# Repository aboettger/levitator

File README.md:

Levitator by RxBConcept on Thingiverse: https://www.thingiverse.com/thing:1966169

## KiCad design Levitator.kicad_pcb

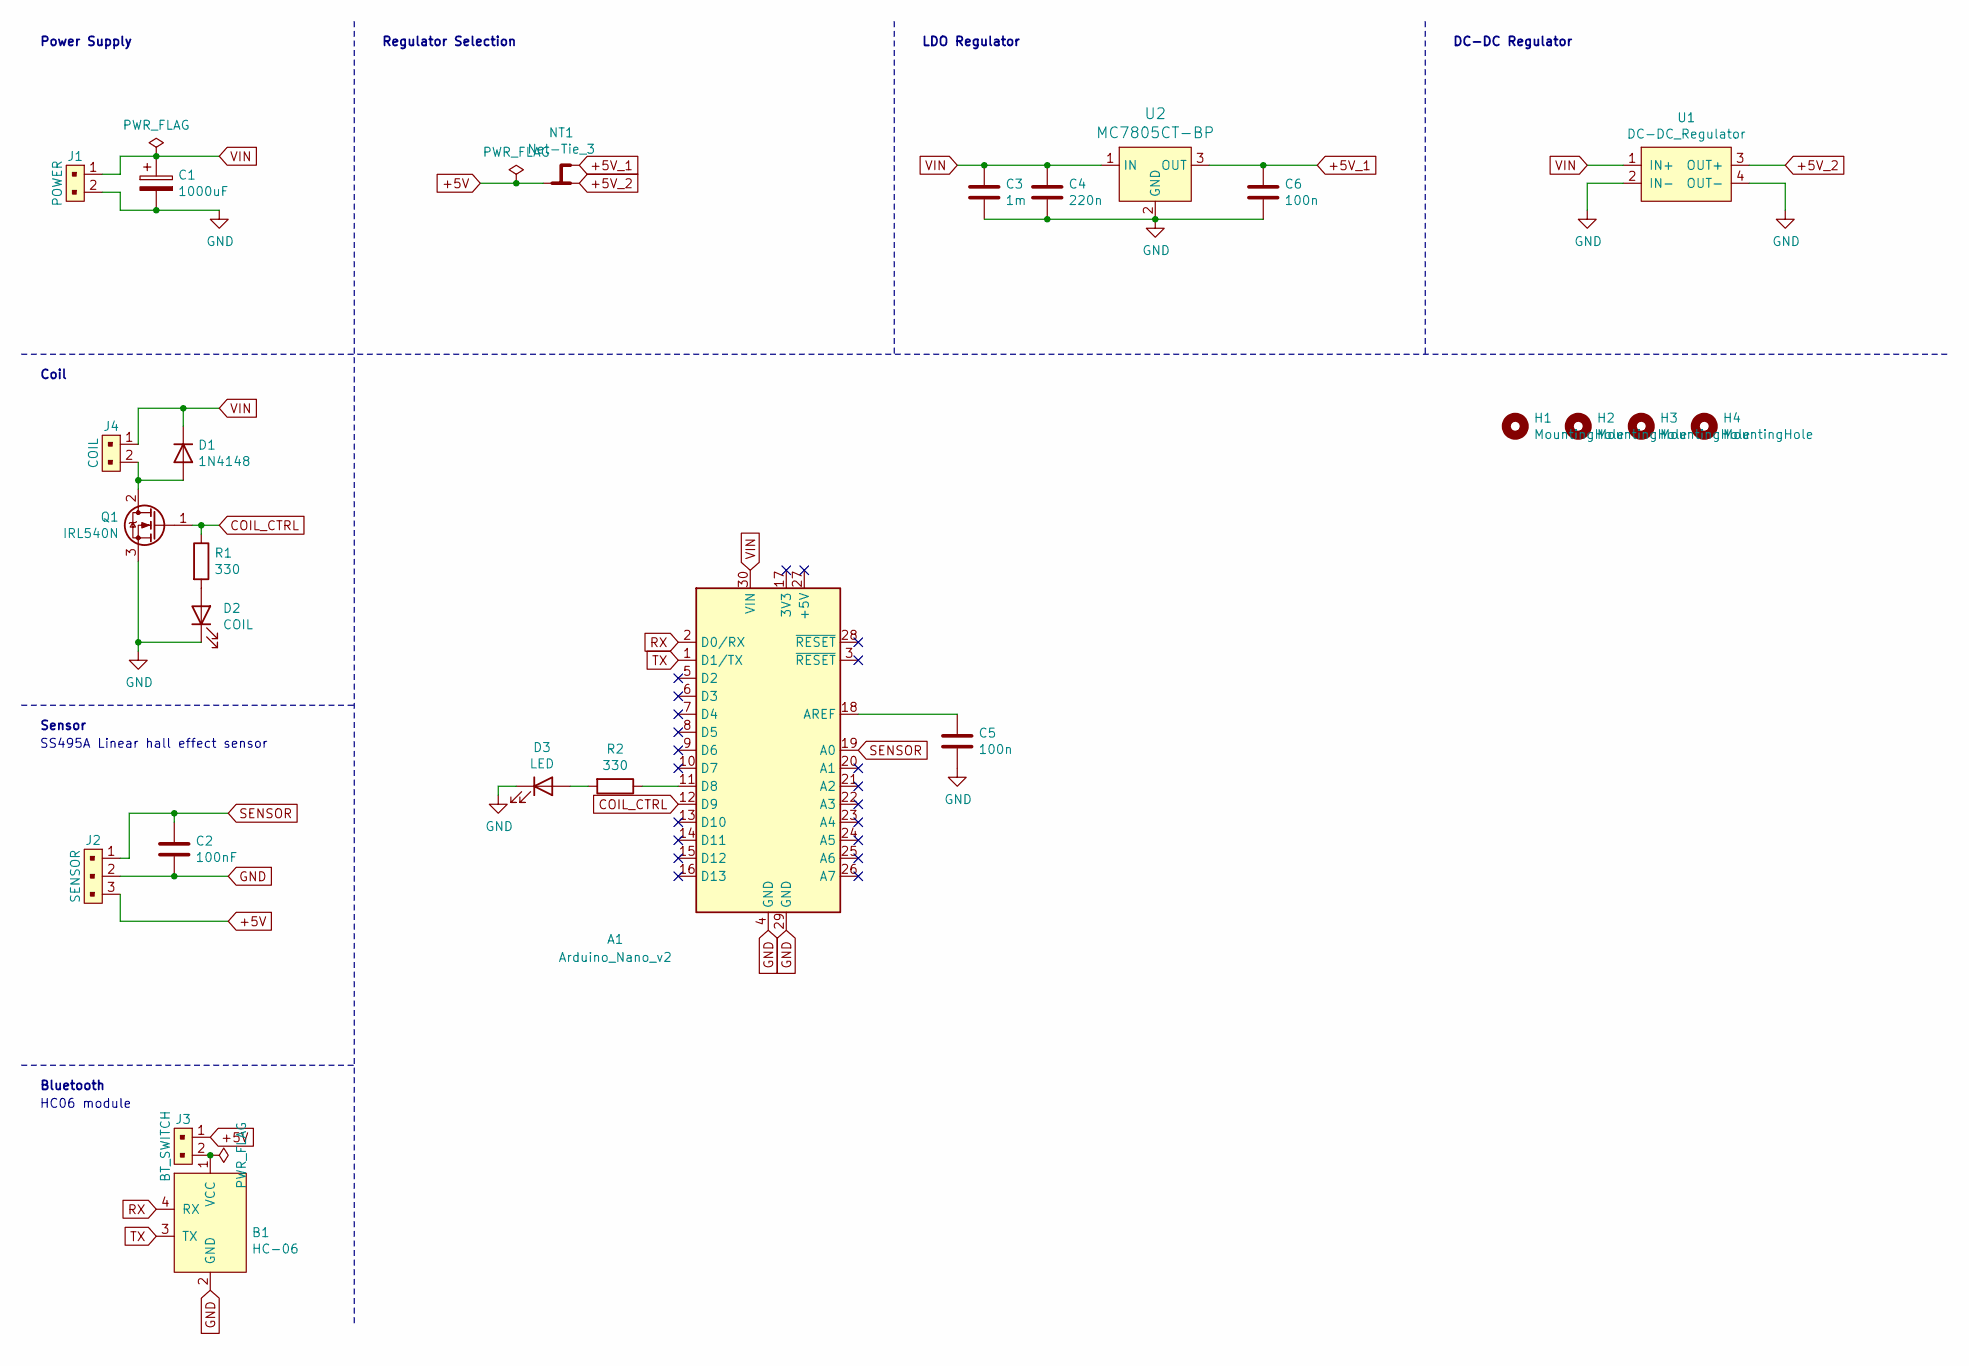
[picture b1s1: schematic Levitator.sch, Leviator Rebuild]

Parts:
A1: Arduino_Nano_v2; Arduino_Nano
B1: HC-06
C1: 1000uF; CP_Radial_D8.0mm_P3.50mm
C2: 100nF; C_Rect_L7.0mm_W2.5mm_P5.00mm
C3: 1m; C_Rect_L7.0mm_W3.5mm_P2.50mm_P5.00mm
C4: 220n; C_Rect_L7.0mm_W3.5mm_P2.50mm_P5.00mm
C5: 100n; C_Rect_L7.0mm_W2.5mm_P5.00mm
C6: 100n; C_Rect_L7.0mm_W3.5mm_P2.50mm_P5.00mm
D1: 1N4148; D_DO-35_SOD27_P7.62mm_Horizontal
D2: COIL; LED_D3.0mm
D3: LED; LED_D3.0mm
H1, H2, H3, H4: MountingHole; MountingHole_3.2mm_M3
J1: POWER; JST_EH_B2B-EH-A_1x02_P2.50mm_Vertical; MPN 22-23-2021; Digi-Key_PN WM4200-ND
J2: SENSOR; JST_EH_B3B-EH-A_1x03_P2.50mm_Vertical
J3: BT_SWITCH; JST_EH_B2B-EH-A_1x02_P2.50mm_Vertical; MPN 22-23-2021; Digi-Key_PN WM4200-ND
J4: COIL; JST_EH_B2B-EH-A_1x02_P2.50mm_Vertical; MPN 22-23-2021; Digi-Key_PN WM4200-ND
NT1: Net-Tie_3; NetTie-3_THT_Pad1.0mm
Q1: IRL540N; TO-220-3_Horizontal_TabDown
R1, R2: 330; R_Axial_DIN0204_L3.6mm_D1.6mm_P7.62mm_Horizontal
U1: DC-DC_Regulator; Board_45x20
U2: MC7805CT-BP; TO-220-3_Horizontal_TabDown; MPN MC7805CT-BP; Digi-Key_PN MC7805CT-BPMS-ND

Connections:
+5V: J2.3, J3.1, NT1.2
+5V_1: C6.1, NT1.3, U2.3 (OUT)
+5V_2: NT1.1, U1.3 (OUT+)
COIL_CTRL: A1.12 (D9), Q1.1 (G), R1.1
GND: A1.4 (GND), A1.29 (GND), B1.2 (GND), C1.2, C2.2, C3.2, C4.2, C5.2, C6.2, D2.1 (K), D3.1 (K), J1.2, J2.2, Q1.3 (S), U1.2 (IN-), U1.4 (OUT-), U2.2 (GND)
unnamed: A1.11 (D8), R2.1
unnamed: A1.18 (AREF), C5.1
unnamed: B1.1 (VCC), J3.2
unnamed: D1.2 (A), J4.2, Q1.2 (D)
unnamed: D2.2 (A), R1.2
unnamed: D3.2 (A), R2.2
RX: A1.2 (D0/RX), B1.4 (RX)
SENSOR: A1.19 (A0), C2.1, J2.1
TX: A1.1 (D1/TX), B1.3 (TX)
VIN: A1.30 (VIN), C1.1, C3.1, C4.1, D1.1 (K), J1.1, J4.1, U1.1 (IN+), U2.1 (IN)

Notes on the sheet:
Power Supply
Coil
Bluetooth
HC06 module
Sensor
SS495A Linear hall effect sensor
Regulator Selection
LDO Regulator
DC-DC Regulator

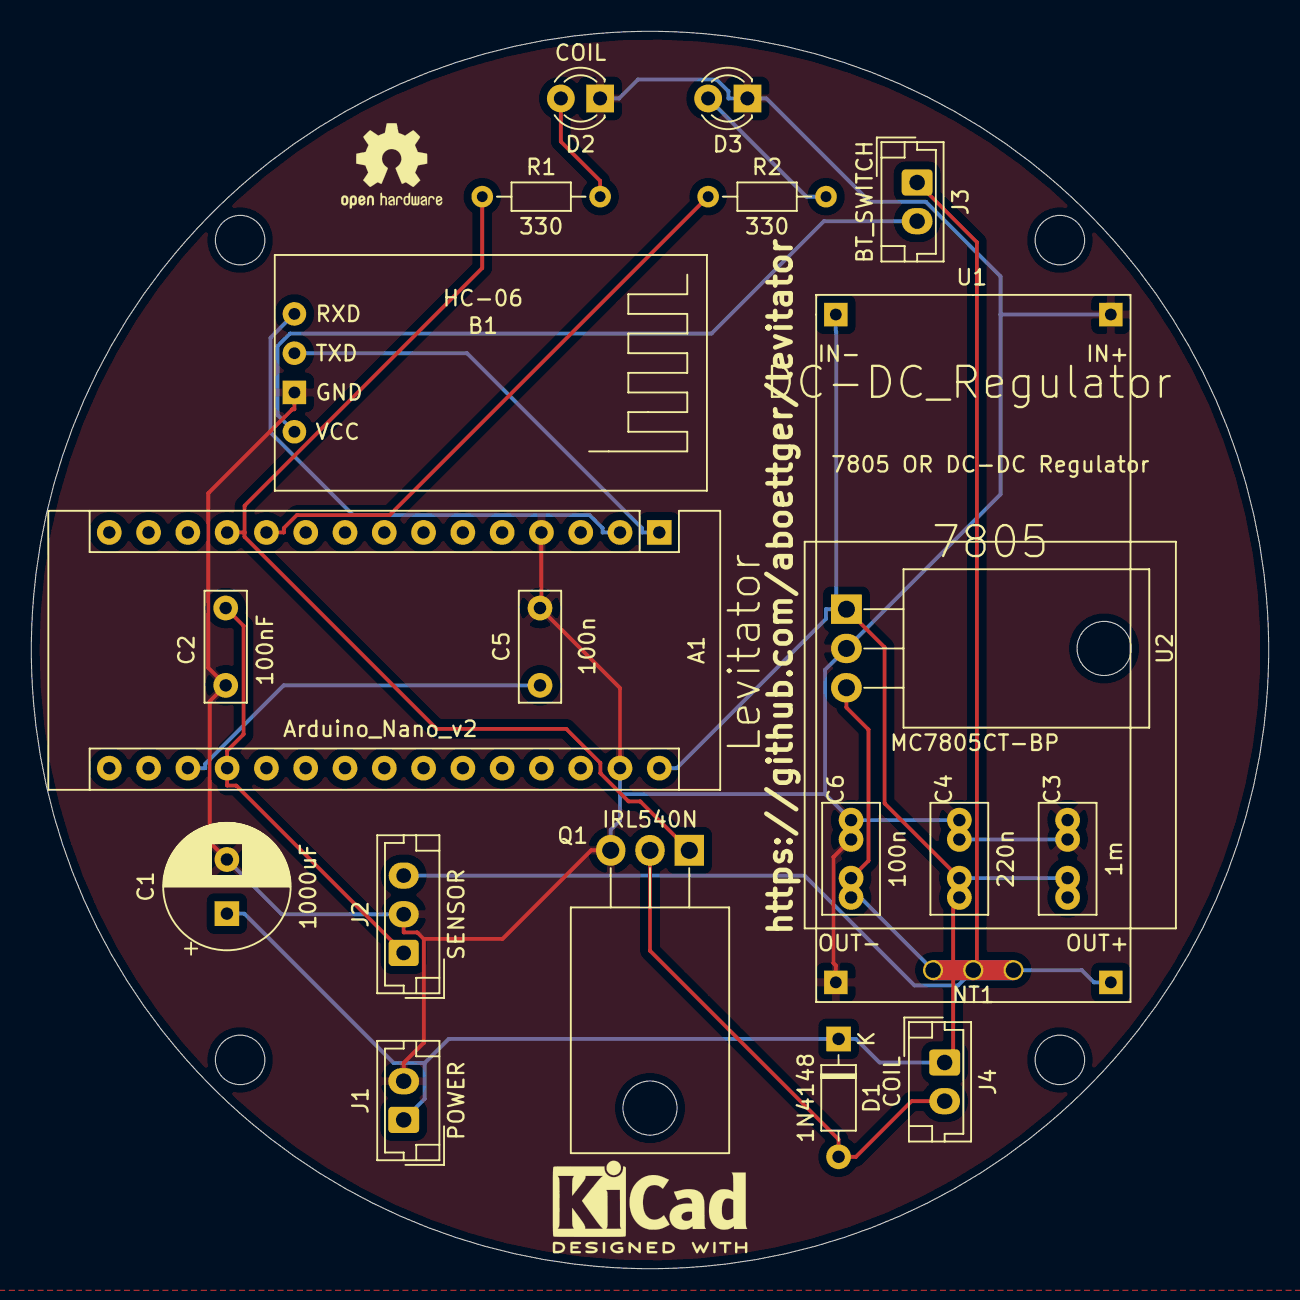
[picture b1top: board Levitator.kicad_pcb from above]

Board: 2 copper layers, 80.0 x 80.0 mm, 26 parts (0 on the bottom side), 15 nets.

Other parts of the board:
OpenHardware: OSHW-Logo2_7.3x6mm_SilkScreen

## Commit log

2020-05-27 Initial
2020-05-28 foobar
2020-05-31 Endspurt
2020-05-31 add gerber
2020-06-02 done
2020-06-02 refresh gerber

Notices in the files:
Levitator.sch:
licensed under cc-nc
